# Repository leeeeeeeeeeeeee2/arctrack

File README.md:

# ArcTrack — Model Rocket Flight Computer

**ArcTrack** is a compact flight computer for model rockets. It logs altitude and
motion to a microSD card, reads GPS, and lets you **live-track the rocket over
WiFi** from your phone. v1.3 adds a power LED, buzzer, and servo header for
nose-cone parachute deploy at apogee.

Designed for a **BT-70** body tube with a 3D-printed nose avionics bay.

**Hardware:** bare **ESP32-C3FH4** (QFN-32, 4MB flash) + 2.4 GHz chip antenna,
USB-C, LiPo charger, 3.3 V regulator, BMP280, MPU-6050, microSD, GPS header,
servo + 5 V boost.

> RF note: chip-antenna matching may need tuning. See `hardware/DESIGN.md`.

## Features

- **Altitude** — BMP280 barometer + apogee detection  
- **Motion** — MPU-6050 IMU (launch / burnout)  
- **GPS** — ATGM336H (UART)  
- **Logging** — microSD CSV  
- **Live tracking** — WiFi AP + phone web dashboard  
- **USB-C** — charge + program (native USB)  
- **1S LiPo** — TP4056 charging  
- **Power LED** — on whenever the board is powered  
- **Buzzer** — beeps (apogee / status)  
- **Servo** — parachute / nose deploy at apogee (5 V boost on board)

## Repo layout

| Path | What |
|------|------|
| `hardware/DESIGN.md` | Electrical design, pinout, power, layout |
| `hardware/BOM.md` | Bill of materials |
| `hardware/WIRING.md` | Pin-by-pin wiring |
| `hardware/kicad/` | PCB project (schematic + board) |
| `hardware/gerbers/` | Fabrication outputs (when exported) |
| `firmware/` | PlatformIO firmware for ESP32-C3 |

## PCB / order

1. Read `hardware/DESIGN.md` and `hardware/WIRING.md`
2. Open the project in `hardware/kicad/`
3. Order boards from **JLCPCB** (4-layer, ~70×40 mm). Use Gerbers from `hardware/gerbers/` when present.
4. Hand-solder: GPS module, battery connector, switch, servo header as needed

## Firmware

```bash
cd firmware
pio run                 # build
pio run -t upload       # flash over USB-C
pio device monitor      # serial logs
```

Phone: join WiFi **`ArcTrack`** / password **`launch123`**, open **http://192.168.4.1**

### Pin map (firmware)

| Function | GPIO |
|----------|------|
| I2C SDA / SCL | 4 / 5 |
| SD SCK / MOSI / MISO / CS | 6 / 7 / 3 / 10 |
| GPS RX / TX | 20 / 21 |
| Buzzer | 0 |
| Servo PWM | 1 |
| Power LED | hardwired to 3.3 V (not a GPIO) |

## Author

Leighton — UK maker / rocketry + electronics builds.

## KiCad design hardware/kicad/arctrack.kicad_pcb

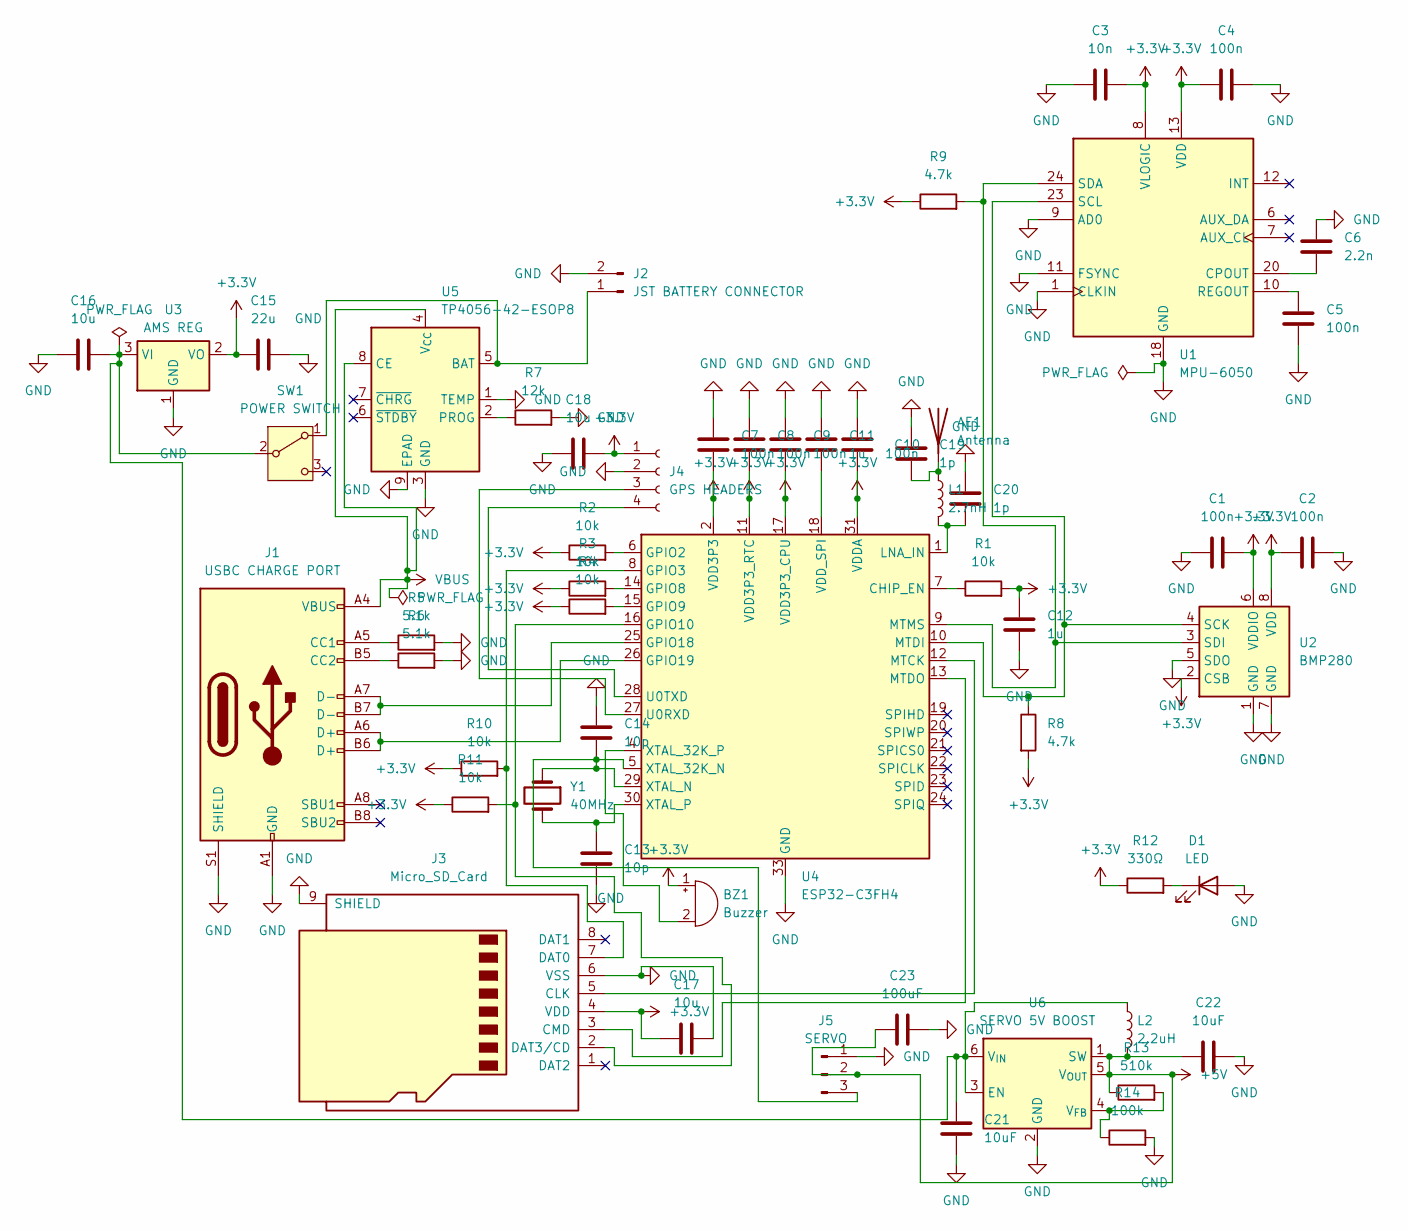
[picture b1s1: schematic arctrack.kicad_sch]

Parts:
AE1: Antenna; Johanson_2450AT43F0100
BZ1: Buzzer; Buzzer_Mallory_AST1109MLTRQ
C1, C2, C4, C5, C7, C8, C9, C10: 100n; C_0402_1005Metric
C3: 10n; C_0402_1005Metric
C6: 2.2n; C_0402_1005Metric
C11, C12: 1u; C_0402_1005Metric
C13, C14: 10p; C_0402_1005Metric
C15: 22u; C_0805_2012Metric
C16, C17, C18: 10u; C_0805_2012Metric
C19, C20: 1p; C_0402_1005Metric
C21, C22: 10uF; C_0805_2012Metric
C23: 100uF; C_0805_2012Metric
D1: LED; LED_0402_1005Metric
J1: USBC CHARGE PORT; USB_C_Receptacle_HRO_TYPE-C-31-M-12
J2: JST BATTERY CONNECTOR; JST_PH_B2B-PH-K_1x02_P2.00mm_Vertical
J3: Micro_SD_Card; microSD_HC_Hirose_DM3AT-SF-PEJM5
J4: GPS HEADERS; PinHeader_1x04_P2.54mm_Vertical
J5: SERVO; PinHeader_1x03_P2.54mm_Vertical
L1: 2.7nH; L_0402_1005Metric
L2: 2.2uH; L_0402_1005Metric
R1, R2, R3, R4, R10, R11: 10k; R_0402_1005Metric
R5, R6: 5.1k; R_0402_1005Metric
R7: 12k; R_0402_1005Metric
R8, R9: 4.7k; R_0402_1005Metric
R12: 330Ω; R_0402_1005Metric
R13: 510k; R_0402_1005Metric
R14: 100k; R_0402_1005Metric
SW1: POWER SWITCH; SW_SPDT_PCM12
U1: MPU-6050; InvenSense_QFN-24_4x4mm_P0.5mm
U2: BMP280; Bosch_LGA-8_2x2.5mm_P0.65mm_ClockwisePinNumbering
U3: AMS REG; SOT-223-3_TabPin2
U4: ESP32-C3FH4; QFN-32-1EP_5x5mm_P0.5mm_EP3.7x3.7mm
U5: TP4056-42-ESOP8; SOIC-8-1EP_3.9x4.9mm_P1.27mm_EP2.41x3.3mm_ThermalVias
U6: SERVO 5V BOOST; SOT-23-6
Y1: 40MHz; Crystal_SMD_2012-2Pin_2.0x1.2mm

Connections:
+3.3V: BZ1.1 (+), C1.2, C2.1, C3.2, C4.1, C7.2, C8.2, C9.2, C10.2, C12.1, C15.1, C17.1, C18.2, J3.4 (VDD), J4.1, R1.2, R2.1, R3.1, R4.1, R8.2, R9.1, R10.1, R11.1, R12.1, U1.8 (VLOGIC), U1.13 (VDD), U2.2 (CSB), U2.6 (VDDIO), U2.8 (VDD), U3.2 (VO), U4.2 (VDD3P3), U4.3 (VDD3P3), U4.11 (VDD3P3_RTC), U4.17 (VDD3P3_CPU), U4.31 (VDDA), U4.32 (VDDA)
+5V: C22.1, C23.1, J5.2, L2.2, R13.1, U6.1 (SW), U6.5 (V_{OUT})
GND: C1.1, C2.2, C3.1, C4.2, C5.2, C6.1, C7.1, C8.1, C9.1, C10.1, C11.1, C12.2, C13.2, C14.1, C15.2, C16.1, C17.2, C18.1, C19.1, C20.2, C21.1, C22.2, C23.2, D1.2 (A), J1.A1 (GND), J1.A12 (GND), J1.B1 (GND), J1.B12 (GND), J1.S1 (SHIELD), J2.2, J3.6 (VSS), J3.9 (SHIELD), J4.2, J5.1, R5.2, R6.2, R7.2, R14.2, U1.1 (CLKIN), U1.9 (AD0), U1.11 (FSYNC), U1.18 (GND), U2.1 (GND), U2.5 (SDO), U2.7 (GND), U3.1 (GND), U4.33 (GND), U5.1 (TEMP), U5.3 (GND), U5.9 (EPAD), U6.2 (GND)
unnamed: AE1.1 (A), C19.2, L1.1
unnamed: BZ1.2 (-), U4.4 (XTAL_32K_P)
unnamed: D1.1 (K), R12.2
unnamed: J1.A5 (CC1), R5.1
unnamed: J1.B5 (CC2), R6.1
unnamed: J2.1, SW1.1 (A), U5.5 (BAT)
unnamed: J3.5 (CLK), U4.12 (MTCK)
unnamed: J3.3 (CMD), U4.13 (MTDO)
unnamed: J3.7 (DAT0), R10.2, U4.8 (GPIO3)
unnamed: J3.2 (DAT3/CD), R11.2, U4.16 (GPIO10)
unnamed: J4.3, U4.27 (U0RXD)
unnamed: J4.4, U4.28 (U0TXD)
unnamed: C14.2, J5.3, U4.5 (XTAL_32K_N), U4.29 (XTAL_N), Y1.1
unnamed: C16.2, C21.2, L2.1, SW1.2 (B), U3.3 (VI), U6.3 (EN), U6.6 (V_{IN})
unnamed: C6.2, U1.20 (CPOUT)
unnamed: C5.1, U1.10 (REGOUT)
unnamed: R8.1, U1.23 (SCL), U2.4 (SCK), U4.10 (MTDI)
unnamed: R9.2, U1.24 (SDA), U2.3 (SDI), U4.9 (MTMS)
unnamed: R1.1, U4.7 (CHIP_EN)
unnamed: R2.2, U4.6 (GPIO2)
unnamed: R3.2, U4.14 (GPIO8)
unnamed: R4.2, U4.15 (GPIO9)
unnamed: J1.A7 (D-), J1.B7 (D-), U4.25 (GPIO18)
unnamed: J1.A6 (D+), J1.B6 (D+), U4.26 (GPIO19)
unnamed: C20.1, L1.2, U4.1 (LNA_IN)
unnamed: C11.2, U4.18 (VDD_SPI)
unnamed: C13.1, U4.30 (XTAL_P), Y1.2
unnamed: R7.1, U5.2 (PROG)
unnamed: R13.2, R14.1, U6.4 (V_{FB})
VBUS: J1.A4 (VBUS), J1.A9 (VBUS), J1.B4 (VBUS), J1.B9 (VBUS), U5.4 (V_{CC}), U5.8 (CE)

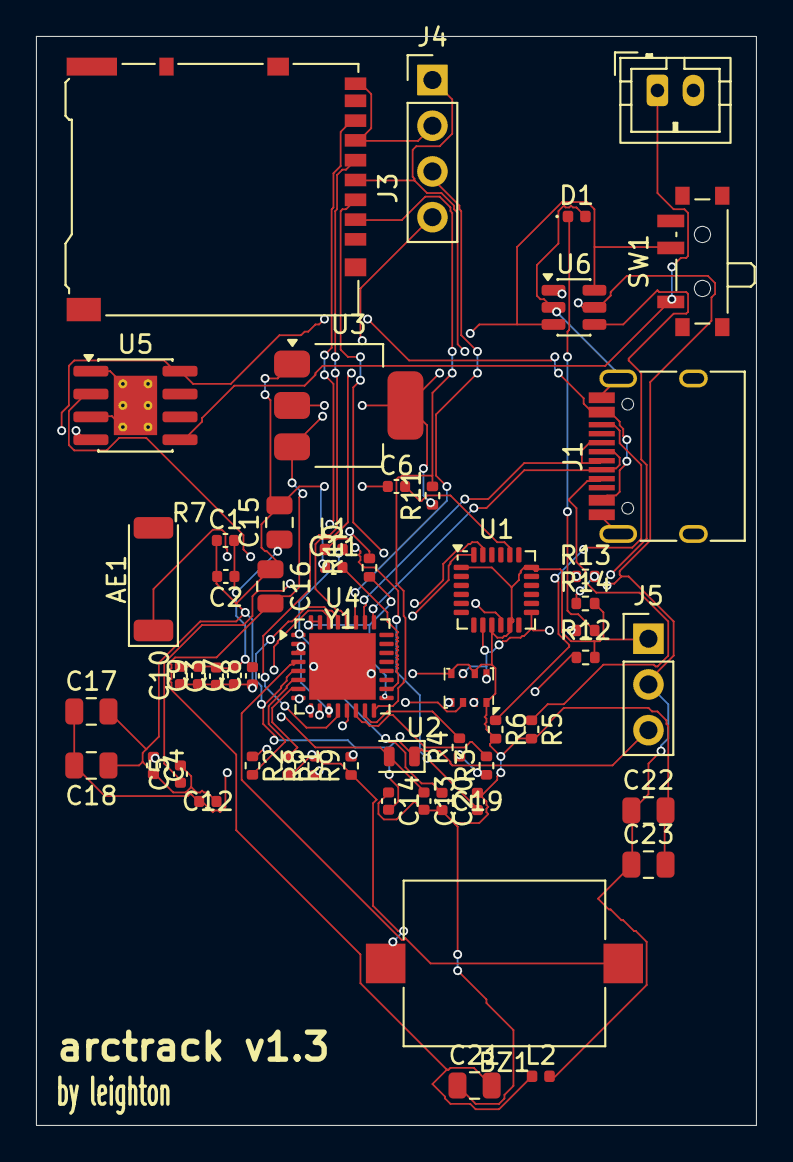
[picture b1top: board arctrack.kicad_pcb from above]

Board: 4 copper layers, 40.0 x 60.5 mm, 55 parts (0 on the bottom side), 33 nets.

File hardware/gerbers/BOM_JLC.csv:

Comment,Designator,Footprint,LCSC Part #
GPS HEADERS,J4,PinHeader_1x04_P2.54mm_Vertical,
Micro_SD_Card,J3,microSD_HC_Hirose_DM3AT-SF-PEJM5,
Antenna,AE1,Johanson_2450AT43F0100,
12k,R7,R_0402_1005Metric,
10k,"R1,R2,R3,R4,R10,R11",R_0402_1005Metric,
100n,"C1,C2,C4,C5,C7,C8,C9,C10",C_0402_1005Metric,
JST BATTERY CONNECTOR,J2,JST_PH_B2B-PH-K_1x02_P2.00mm_Vertical,
2.7nH,L1,L_0402_1005Metric,
AMS REG,U3,SOT-223-3_TabPin2,
4.7k,"R8,R9",R_0402_1005Metric,
1p,"C19,C20",C_0402_1005Metric,
40MHz,Y1,Crystal_SMD_2012-2Pin_2.0x1.2mm,
5.1k,"R5,R6",R_0402_1005Metric,
1u,"C11,C12",C_0402_1005Metric,
10u,"C16,C17,C18",C_0805_2012Metric,
22u,C15,C_0805_2012Metric,
2.2n,C6,C_0402_1005Metric,
10p,"C13,C14",C_0402_1005Metric,
10n,C3,C_0402_1005Metric,
TP4056,U5,SOIC-8-1EP_3.9x4.9mm_P1.27mm_EP2.41x3.3mm_ThermalVias,
USBC CHARGE PORT,J1,USB_C_Receptacle_HRO_TYPE-C-31-M-12,
POWER SWITCH,SW1,SW_SPDT_PCM12,
BMP280,U2,Bosch_LGA-8_2x2.5mm_P0.65mm_ClockwisePinNumbering,
ESP32-C3FH4,U4,QFN-32-1EP_5x5mm_P0.5mm_EP3.7x3.7mm,
MPU-6050,U1,InvenSense_QFN-24_4x4mm_P0.5mm,
SERVO 5V BOOST,U6,SOT-23-6,
330,R12,R_0402_1005Metric,
2.2uH,L2,L_0402_1005Metric,
100k,R14,R_0402_1005Metric,
SERVO,J5,PinHeader_1x03_P2.54mm_Vertical,
100uF,C23,C_0805_2012Metric,
10uF,"C21,C22",C_0805_2012Metric,
Buzzer,BZ1,Buzzer_Mallory_AST1109MLTRQ,
LED,D1,LED_0402_1005Metric,
510k,R13,R_0402_1005Metric,
